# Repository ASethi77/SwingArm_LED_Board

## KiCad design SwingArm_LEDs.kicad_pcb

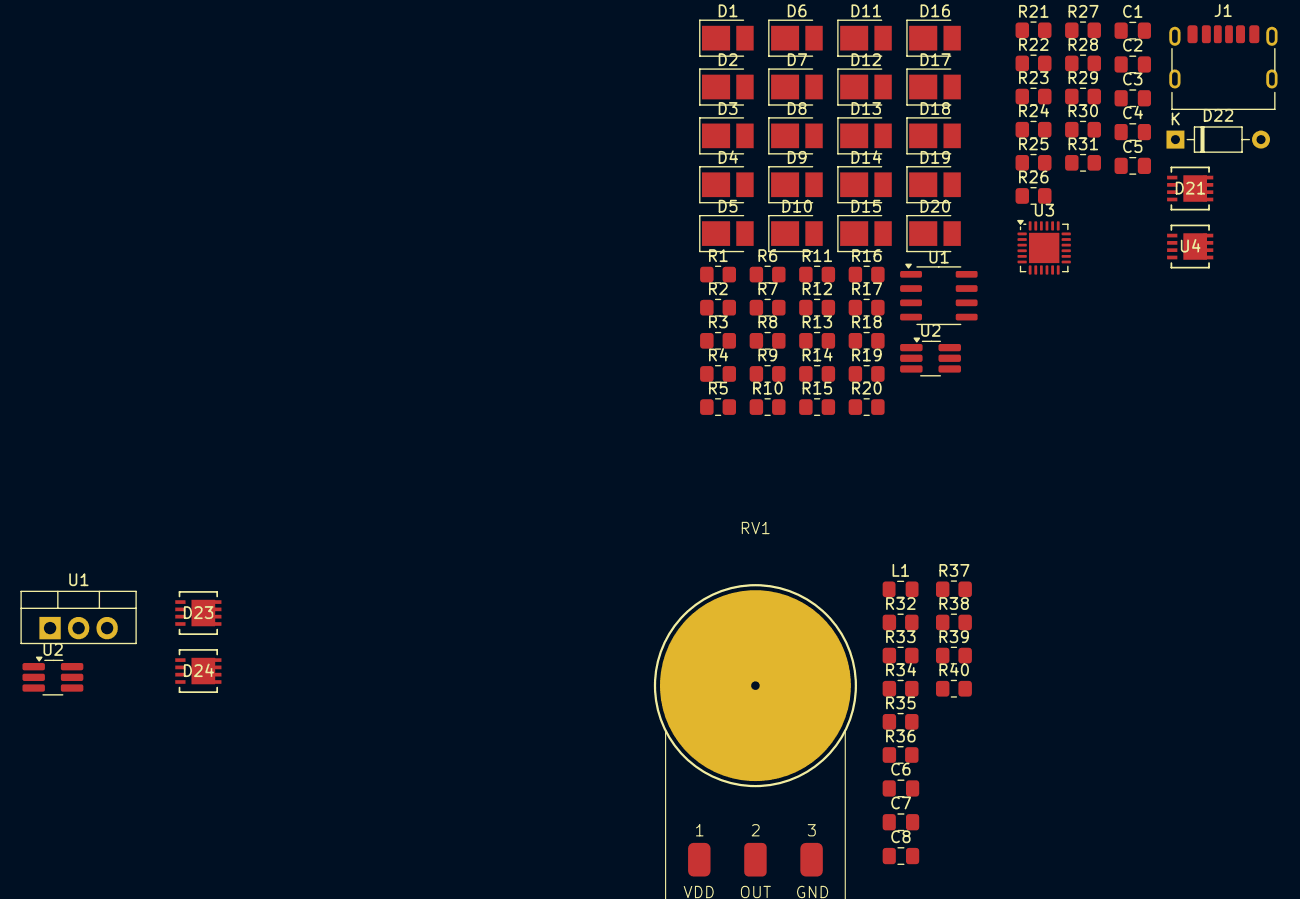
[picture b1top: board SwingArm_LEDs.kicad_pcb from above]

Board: 2 copper layers, 81 parts (0 on the bottom side), 63 nets, no tracks yet.

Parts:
C1: 100nF; C_0805_2012Metric_Pad1.18x1.45mm_HandSolder
C2, C3, C4, C5: 1uF; C_0805_2012Metric_Pad1.18x1.45mm_HandSolder
C6: 10nF; C_0805_2012Metric_Pad1.18x1.45mm_HandSolder
C7, C8: 10uF; C_0805_2012Metric_Pad1.18x1.45mm_HandSolder
D1, D2, D3, D4, D5, D6, D7, D8, D9, D10, D11, D12, D13, D14, D15, D16, D17, D18, D19, D20: LED; LED_PLCC_2835_Handsoldering
D21, D23, D24: ESDA25P35-1U1M; TVS_ESDA25P35-1U1M
D22: 1N4148; D_DO-35_SOD27_P7.62mm_Horizontal
J1: USB_C_Receptacle; USB_C_Receptacle_HRO_TYPE-C-31-M-17
L1: 4.7uH; L_0805_2012Metric_Pad1.15x1.40mm_HandSolder
R1, R2, R3, R4, R5, R6, R7, R8, R9, R10, R11, R12, R13, R14, R15, R16, R17, R18, R19, R20: 5R; R_0805_2012Metric_Pad1.20x1.40mm_HandSolder
R21: 10k; R_0805_2012Metric_Pad1.20x1.40mm_HandSolder
R22, R32, R33, R34: 100k; R_0805_2012Metric_Pad1.20x1.40mm_HandSolder
R23, R40: 22k; R_0805_2012Metric_Pad1.20x1.40mm_HandSolder
R24, R25, R26, R27, R35, R36: 0; R_0805_2012Metric_Pad1.20x1.40mm_HandSolder
R28: 100; R_0805_2012Metric_Pad1.20x1.40mm_HandSolder
R29, R30, R37: 1k; R_0805_2012Metric_Pad1.20x1.40mm_HandSolder
R31: 470; R_0805_2012Metric_Pad1.20x1.40mm_HandSolder
R38: 150mR; R_0805_2012Metric_Pad1.20x1.40mm_HandSolder
R39: 68k; R_0805_2012Metric_Pad1.20x1.40mm_HandSolder
RV1: R_Potentiometer; PDB181_K420F_103C
U1: LM7815_TO220; TO-220-3_Vertical
U1#2: ICM7555xB; SOIC-8_3.9x4.9mm_P1.27mm
U2: TSOT-23-6_HandSoldering
U2#2: MP2410AG-Z; TSOT-23-6_HandSoldering
U3: STUSB4500QTR; QFN-24-1EP_4x4mm_P0.5mm_EP2.7x2.7mm
U4: STL6P3LLH6; POWERFLAT_3P3X3P3_STM

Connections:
+15V: R39.1, U1.3 (VO)
/LED-: C8.1, D17.1 (K), D18.1 (K), D19.1 (K), D20.1 (K), R37.1, R38.1
/LED_DIM: RV1.2, U2#2.5 (EN/DIM)
/USB_C_PD_Input/ADDR0: R33.1, R35.2, U3.12 (ADDR0)
/USB_C_PD_Input/ADDR1: R32.1, R36.2, U3.13 (ADDR1)
/USB_C_PD_Input/CC1: J1.A5 (CC1), R24.2, U3.2 (CC1)
/USB_C_PD_Input/CC1_DEAD_BAT_ENB: R24.1, R26.1, U3.1 (CC1DB)
/USB_C_PD_Input/CC2: J1.B5 (CC2), R27.2, U3.4 (CC2)
/USB_C_PD_Input/CC2_DEAD_BAT_ENB: R25.1, R27.1, U3.5 (CC2DB)
/USB_C_PD_Input/RST: R21.1, R34.1, U3.6 (RESET)
/USB_C_PD_Input/VBUS_VS_DISCH: R30.2, U3.18 (VBUS_VS_DISCH)
/USB_C_PD_Input/VREG_1v2: C3.1, U3.21 (VREG_1V2)
/USB_C_PD_Input/VREG_2v7: C4.1, R35.1, R36.1, U3.23 (VREG_2V7)
/USB_C_PD_Input/VSNK: C1.1, C7.2, R29.2, U1.1 (VI), U2#2.3 (VIN), U4.5 (D)
GND: C2.2, C3.2, C4.2, C5.2, C7.1, J1.A12 (GND), J1.B12 (GND), J1.S1 (SHIELD), R21.2, R25.2, R26.2, R32.2, R33.2, R34.2, R38.2, RV1.3, U1.2 (GND), U2#2.1 (GND), U3.7 (SCL), U3.8 (SDA), U3.10 (GND), U3.22 (VSYS), U3.25 (GND)
LED+: C8.2, L1.2, R1.1, R2.1, R3.1, R4.1
unnamed: C1.2, R28.2
unnamed: D1.2 (A), R1.2
unnamed: D1.1 (K), R5.1
unnamed: D2.2 (A), R2.2
unnamed: D2.1 (K), R6.1
unnamed: D3.2 (A), R3.2
unnamed: D3.1 (K), R7.1
unnamed: D4.2 (A), R4.2
unnamed: D4.1 (K), R8.1
unnamed: D5.2 (A), R5.2
unnamed: D5.1 (K), R9.1
unnamed: D6.2 (A), R6.2
unnamed: D6.1 (K), R10.1
unnamed: D7.2 (A), R7.2
unnamed: D7.1 (K), R11.1
unnamed: D8.2 (A), R8.2
unnamed: D8.1 (K), R12.1
unnamed: D9.2 (A), R9.2
unnamed: D9.1 (K), R13.1
unnamed: D10.2 (A), R10.2
unnamed: D10.1 (K), R14.1
unnamed: D11.2 (A), R11.2
unnamed: D11.1 (K), R15.1
unnamed: D12.2 (A), R12.2
unnamed: D12.1 (K), R16.1
unnamed: D13.2 (A), R13.2
unnamed: D13.1 (K), R17.1
unnamed: D14.2 (A), R14.2
unnamed: D14.1 (K), R18.1
unnamed: D15.2 (A), R15.2
unnamed: D15.1 (K), R19.1
unnamed: D16.2 (A), R16.2
unnamed: D16.1 (K), R20.1
unnamed: D17.2 (A), R17.2
unnamed: D18.2 (A), R18.2
unnamed: D19.2 (A), R19.2
unnamed: D20.2 (A), R20.2
unnamed: C2.1, D22.1 (K), R30.1, R31.2
unnamed: R39.2, R40.1
unnamed: R40.2, RV1.1
unnamed: C6.1, U2#2.6 (BST)
unnamed: R37.2, U2#2.4 (FB)
unnamed: C6.2, L1.1, U2#2.2 (SW)
unnamed: R29.1, U3.9 (DISCH)
unnamed: R23.2, U3.16 (VBUS_EN_SNK)
unnamed: R22.2, R23.1, R28.1, U4.4 (G)
VBUS: C5.1, D22.2 (A), J1.A9 (VBUS), J1.B9 (VBUS), R22.1, R31.1, U3.24 (VDD), U4.3 (S)

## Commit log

2024-08-13 Schematics mostly done? Missing a few pins for STUSB4500QTR
2024-08-19 Add usb c power + led driver
2024-08-19 Fix ERC
2024-08-19 cleanup
2024-10-24 Fixup resistor values
2024-11-17 Fix capacitor value
